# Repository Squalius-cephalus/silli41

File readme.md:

# Silli41

Silli41 is 41-key column staggered keyboard, heavily based on [REVIUNG41](https://github.com/gtips/reviung "REVIUNG41") design.

PCB is designed for MX style keyswitches, but it should support Choc V2 switches too. Current top plate only supports MX style switches. 5-pin switches is supported.

[QMK](https://github.com/qmk/qmk_firmwarehttp:// "QMK") and [Vial](https://github.com/vial-kb/vial-qmk "Vial") firmwares has very barebones keymapping. Good for quick testing, but there is my current layout for Vial firmare. It is designed for a Finnish layout.

### Bill of materials
- 41x MX compatible keyswitches
- 40x 1u keycaps
- 1x 1.75u keycap
- 41x diodes
- 1x Raspberry Pi Pico or pin compatible clone
- 14x M2 Heat set inserts, length 2mm(OD3.2mm)
- 14x M2 bolts, length 4mm
- 1x PCB
- 1x Bottom plate
- 1x Top plate(optional)

PCB design uses footprints from [ScottoKeebs](https://github.com/joe-scotto/scottokeebs/tree/main/Extras/ScottoKicad "ScottoKeebs") and [kbd library.](https://github.com/foostan/kbd "kbd library.")

### TODO
1. Build guide
2. Redo traces
3. Split the top plate in two

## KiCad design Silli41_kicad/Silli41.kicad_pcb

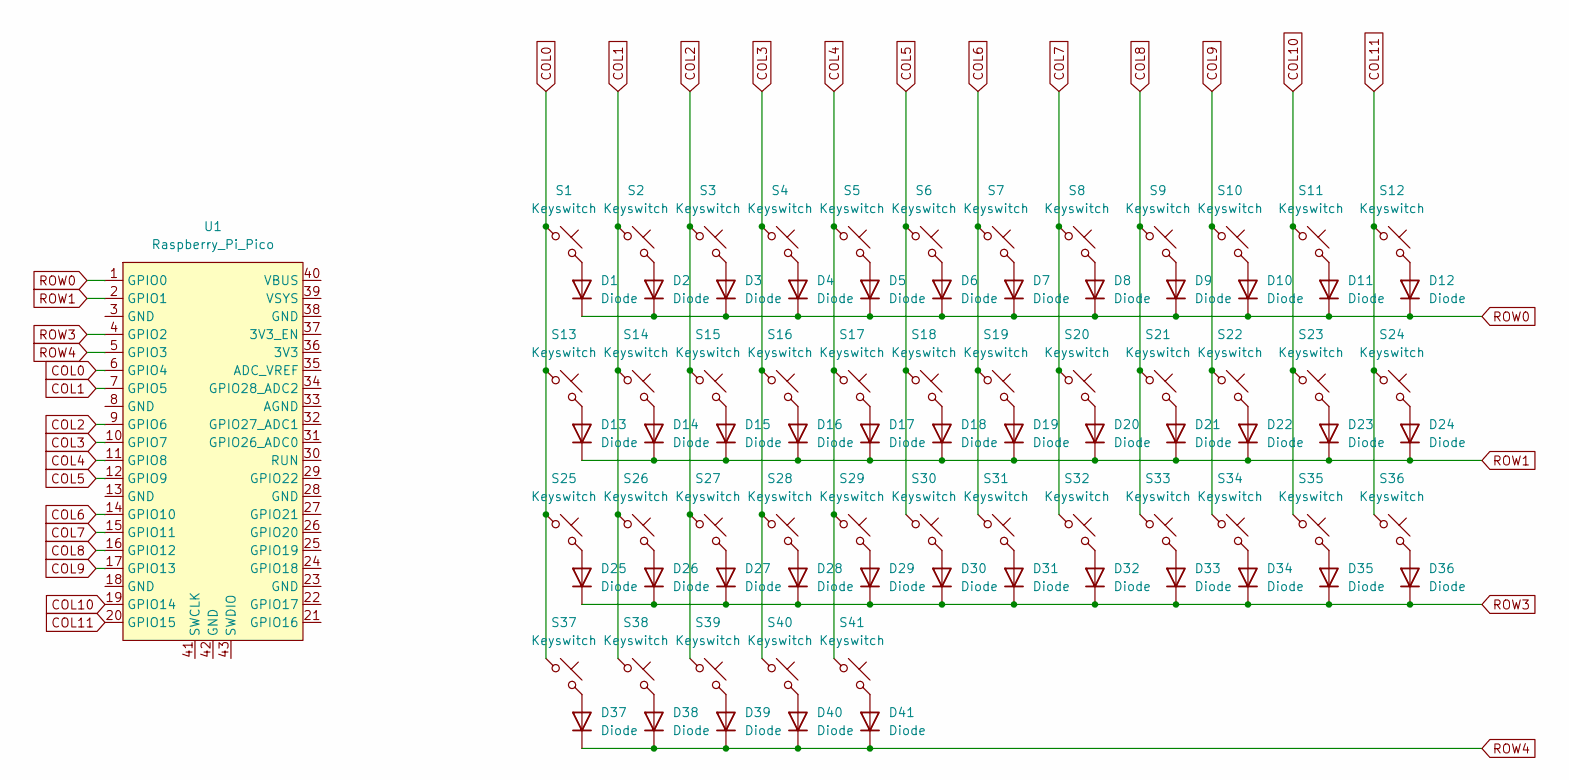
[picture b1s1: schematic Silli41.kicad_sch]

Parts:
D1, D2, D3, D4, D5, D6, D7, D8, D9, D10, D11, D12, D13, D14, D15, D16, D17, D18, D19, D20, D21, D22, D23, D24, D25, D26, D27, D28, D29, D30, D31, D32, D33, D34, D35, D36, D37, D38, D39, D40, D41: Diode; Diode_DO-35
S1, S2, S3, S4, S5, S6, S7, S8, S9, S10, S11, S12, S13, S14, S15, S16, S17, S18, S19, S20, S21, S22, S23, S24, S25, S26, S27, S28, S29, S30, S31, S32, S33, S34, S35, S36, S37, S38, S39, S40, S41: Keyswitch; CherryMX_ChocV2_1u
U1: Raspberry_Pi_Pico

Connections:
COL0: S1.1, S13.1, S25.1, S37.1, U1.6 (GPIO4)
COL1: S2.1, S14.1, S26.1, S38.1, U1.7 (GPIO5)
COL2: S3.1, S15.1, S27.1, S39.1, U1.9 (GPIO6)
COL3: S4.1, S16.1, S28.1, S40.1, U1.10 (GPIO7)
COL4: S5.1, S17.1, S29.1, S41.1, U1.11 (GPIO8)
COL5: S6.1, S18.1, S30.1, U1.12 (GPIO9)
COL6: S7.1, S19.1, S31.1, U1.14 (GPIO10)
COL7: S8.1, S20.1, S32.1, U1.15 (GPIO11)
COL8: S9.1, S21.1, S33.1, U1.16 (GPIO12)
COL9: S10.1, S22.1, S34.1, U1.17 (GPIO13)
COL10: S11.1, S23.1, S35.1, U1.19 (GPIO14)
COL11: S12.1, S24.1, S36.1, U1.20 (GPIO15)
unnamed: D1.2 (A), S1.2
unnamed: D2.2 (A), S2.2
unnamed: D3.2 (A), S3.2
unnamed: D4.2 (A), S4.2
unnamed: D5.2 (A), S5.2
unnamed: D6.2 (A), S6.2
unnamed: D7.2 (A), S7.2
unnamed: D8.2 (A), S8.2
unnamed: D9.2 (A), S9.2
unnamed: D10.2 (A), S10.2
unnamed: D11.2 (A), S11.2
unnamed: D12.2 (A), S12.2
unnamed: D13.2 (A), S13.2
unnamed: D14.2 (A), S14.2
unnamed: D15.2 (A), S15.2
unnamed: D16.2 (A), S16.2
unnamed: D17.2 (A), S17.2
unnamed: D18.2 (A), S18.2
unnamed: D19.2 (A), S19.2
unnamed: D20.2 (A), S20.2
unnamed: D21.2 (A), S21.2
unnamed: D22.2 (A), S22.2
unnamed: D23.2 (A), S23.2
unnamed: D24.2 (A), S24.2
unnamed: D25.2 (A), S25.2
unnamed: D26.2 (A), S26.2
unnamed: D27.2 (A), S27.2
unnamed: D28.2 (A), S28.2
unnamed: D29.2 (A), S29.2
unnamed: D30.2 (A), S30.2
unnamed: D31.2 (A), S31.2
unnamed: D32.2 (A), S32.2
unnamed: D33.2 (A), S33.2
unnamed: D34.2 (A), S34.2
unnamed: D35.2 (A), S35.2
unnamed: D36.2 (A), S36.2
unnamed: D37.2 (A), S37.2
unnamed: D38.2 (A), S38.2
unnamed: D39.2 (A), S39.2
unnamed: D40.2 (A), S40.2
unnamed: D41.2 (A), S41.2
ROW0: D1.1 (K), D2.1 (K), D3.1 (K), D4.1 (K), D5.1 (K), D6.1 (K), D7.1 (K), D8.1 (K), D9.1 (K), D10.1 (K), D11.1 (K), D12.1 (K), U1.1 (GPIO0)
ROW1: D13.1 (K), D14.1 (K), D15.1 (K), D16.1 (K), D17.1 (K), D18.1 (K), D19.1 (K), D20.1 (K), D21.1 (K), D22.1 (K), D23.1 (K), D24.1 (K), U1.2 (GPIO1)
ROW3: D25.1 (K), D26.1 (K), D27.1 (K), D28.1 (K), D29.1 (K), D30.1 (K), D31.1 (K), D32.1 (K), D33.1 (K), D34.1 (K), D35.1 (K), D36.1 (K), U1.4 (GPIO2)
ROW4: D37.1 (K), D38.1 (K), D39.1 (K), D40.1 (K), D41.1 (K), U1.5 (GPIO3)

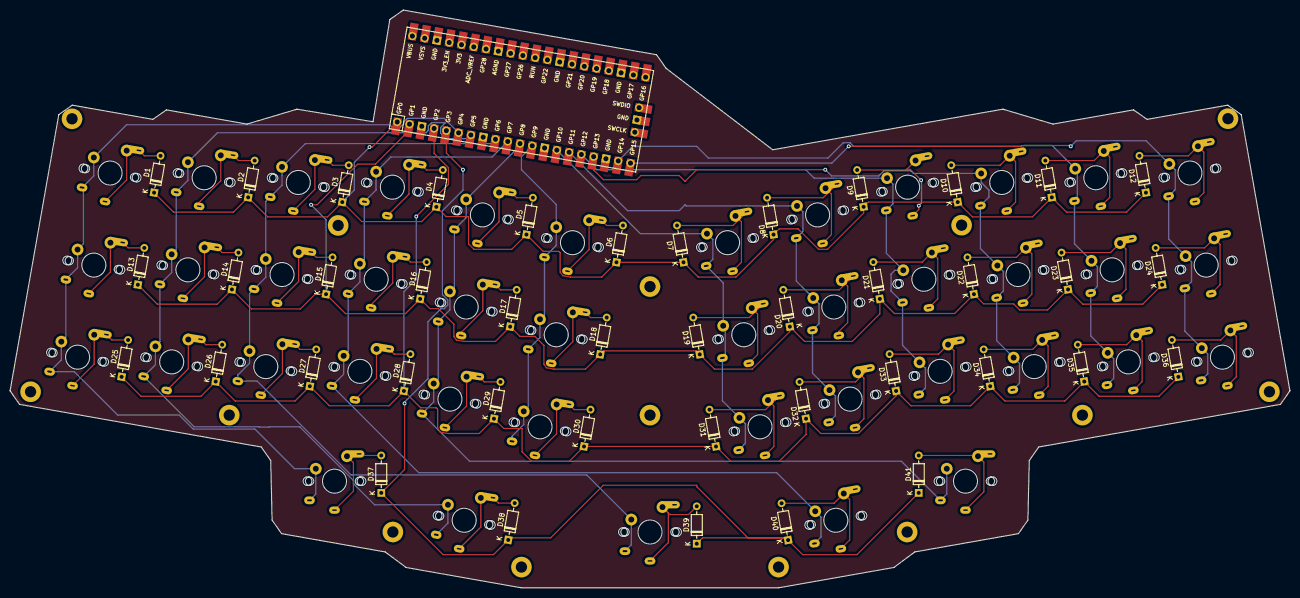
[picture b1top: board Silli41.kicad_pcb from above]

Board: 2 copper layers, 260.8 x 117.7 mm, 83 parts (0 on the bottom side), 57 nets.

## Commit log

2024-03-17 Gerber files added and readme
2024-03-22 Bottom plate can be printed now in two pieces
2024-03-25 Added KiCAD files
2024-03-25 Updated top plate scale
